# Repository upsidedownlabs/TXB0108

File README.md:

# Upside Down Labs - TXB0108

TXB0108 is 8-Bit Bidirectional Voltage-Level Translator with Auto-Direction Sensing and ±15-kV ESD Protection. 

### TXB0108DQSR Breakout Board

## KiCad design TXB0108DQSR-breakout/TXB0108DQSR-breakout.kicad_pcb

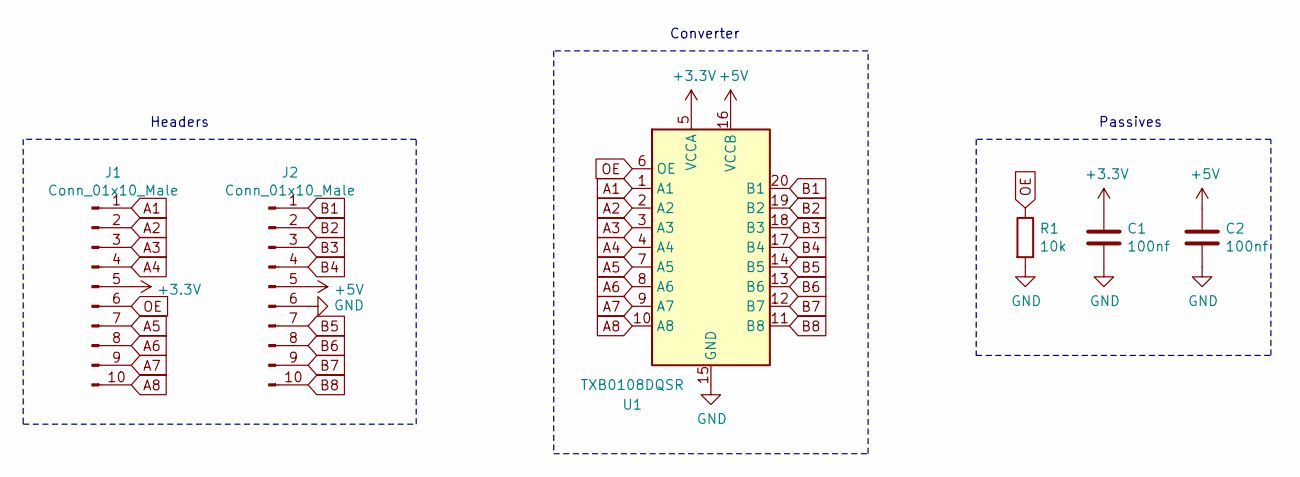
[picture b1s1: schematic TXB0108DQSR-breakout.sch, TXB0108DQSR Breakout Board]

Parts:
C1, C2: 100nf; C_0805_2012Metric_Pad1.18x1.45mm_HandSolder
J1, J2: Conn_01x10_Male; PinHeader_1x10_P2.54mm_Vertical
R1: 10k; R_0805_2012Metric_Pad1.20x1.40mm_HandSolder
U1: TXB0108DQSR; USON-20_2x4mm_P0.4mm

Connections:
+3V3: C1.1, J1.5, U1.5 (VCCA)
+5V: C2.1, J2.5, U1.16 (VCCB)
A1: J1.1, U1.1 (A1)
A2: J1.2, U1.2 (A2)
A3: J1.3, U1.3 (A3)
A4: J1.4, U1.4 (A4)
A5: J1.7, U1.7 (A5)
A6: J1.8, U1.8 (A6)
A7: J1.9, U1.9 (A7)
A8: J1.10, U1.10 (A8)
B1: J2.1, U1.20 (B1)
B2: J2.2, U1.19 (B2)
B3: J2.3, U1.18 (B3)
B4: J2.4, U1.17 (B4)
B5: J2.7, U1.14 (B5)
B6: J2.8, U1.13 (B6)
B7: J2.9, U1.12 (B7)
B8: J2.10, U1.11 (B8)
GND: C1.2, C2.2, J2.6, R1.2, U1.15 (GND)
OE: J1.6, R1.1, U1.6 (OE)

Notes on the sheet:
Headers
Converter
Passives

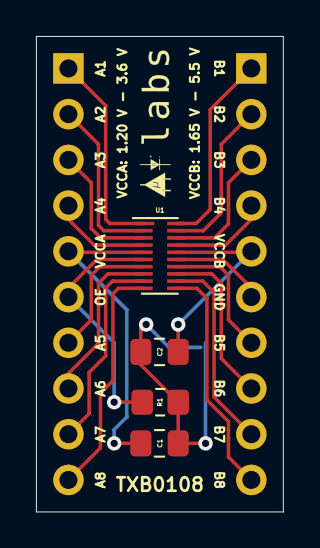
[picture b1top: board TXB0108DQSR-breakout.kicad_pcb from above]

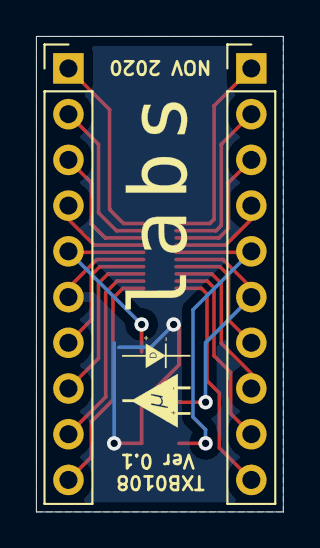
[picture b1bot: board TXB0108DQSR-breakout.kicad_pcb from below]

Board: 2 copper layers, 13.7 x 26.4 mm, 6 parts (2 on the bottom side), 20 nets.

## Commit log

2020-11-03 add datasheet
2020-11-03 add v0.1 of PCB
2020-11-14 Update project
2020-11-14 Add schematic as pdf
